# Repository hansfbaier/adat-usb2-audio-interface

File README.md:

# ADAT USB Audio Interface

FPGA based USB 2.0 High Speed audio interface featuring multiple optical ADAT inputs and outputs

## Status / current limitations
* Enumerates as class compliant audio device on Windows and Linux (Mac OS not tested). 2 and 32 channel modes.
* Audio input and output seems to work glitch free.
* Only 48kHz sample rate supported
* Integrated USB2 high speed logic analyzer works
* Runs without dropouts with FlexASIO with a buffer size of 32 samples (0.67ms latency)
* Has a hardware roundtrip latency (USB out -> ADAT out -> cable -> ADAT in -> USB in)
  of 2-3 USB2 microframes which is about 0.25ms to 0.375 ms
* Both headphone DACs on the board work now. In two channel mode, they are both wired to channels 0/1.
  In 36 channel mode DAC1 is wired to channels 0/1 and DAC2 to channels 2/3
* Both USB PHYs now are operational. USB1 has access to all 32 ADAT I/Os and has 4 extra channels to/from USB2.
  USB2 enumerates as a 4-channel sound card which sends/receives audio to/from USB1
* Both USB interfaces will also enumerate as USB MIDI devices and send each other MIDI
* The current board design has not been designed with the case in mind: In the current version of the case,
  only ADAT-cables with thin connectors will fit into the holes. Cables with fat connectors will hit the case
  wall before they can be fully inserted. This will be fixed in a future iteration of the PCB and case.
* The current case design lacks a guide channel for the LED light pipes. Therefore there is considerable bleed
  from lightpipes into each other, and they also can't be positioned exactly over the LEDs.
  Will be fixed in the next version of the case.
* Limitation: Currently audio input will not work properly when audio output is inactive.
  This should not be a problem for most uses (VoIP, Videoconference, DAW recording).
  If you have an important use case which needs this, please file an issue.

## Hardware
The current board design is a custom development board,
based on the QMTech core FPGA boards.
Once the chip shortage is over, it is planned to move to
a complete custom design, including the FPGA.

## How to build
1. Download and install [Intel Quartus Lite](https://fpgasoftware.intel.com/?edition=lite)
2. put the bin/ directory of Quartus into your PATH variable:
```bash
export PATH=$PATH:/opt/intelFPGA_lite/21.1/quartus/bin/
```
Of course you need to adjust this to the install directory and version of your particular installation.

3. Set up python venv and install requirements:
```bash
$ cd gateware/
$ ./initialize-python-environment.sh
$ cd ..
```

4. Activate the venv and build
```bash
$ source ./gateware/venv/bin/activate
$ python3 gateware/adat_usb2_audio_interface.py --keep
```

This will create a directory named build/ and after a successful build will directly
try to load the generated bitstream into the FPGA, if an USB-Blaster is connected.
Or, you can flash the bitstream manually, by opening the Quartus GUI with:
```bash
quartus build/*.qpf
```
and then open the programmer application from there.
Alternatively you could directly start the programmer with:
```bash
quartus_pgmw
```

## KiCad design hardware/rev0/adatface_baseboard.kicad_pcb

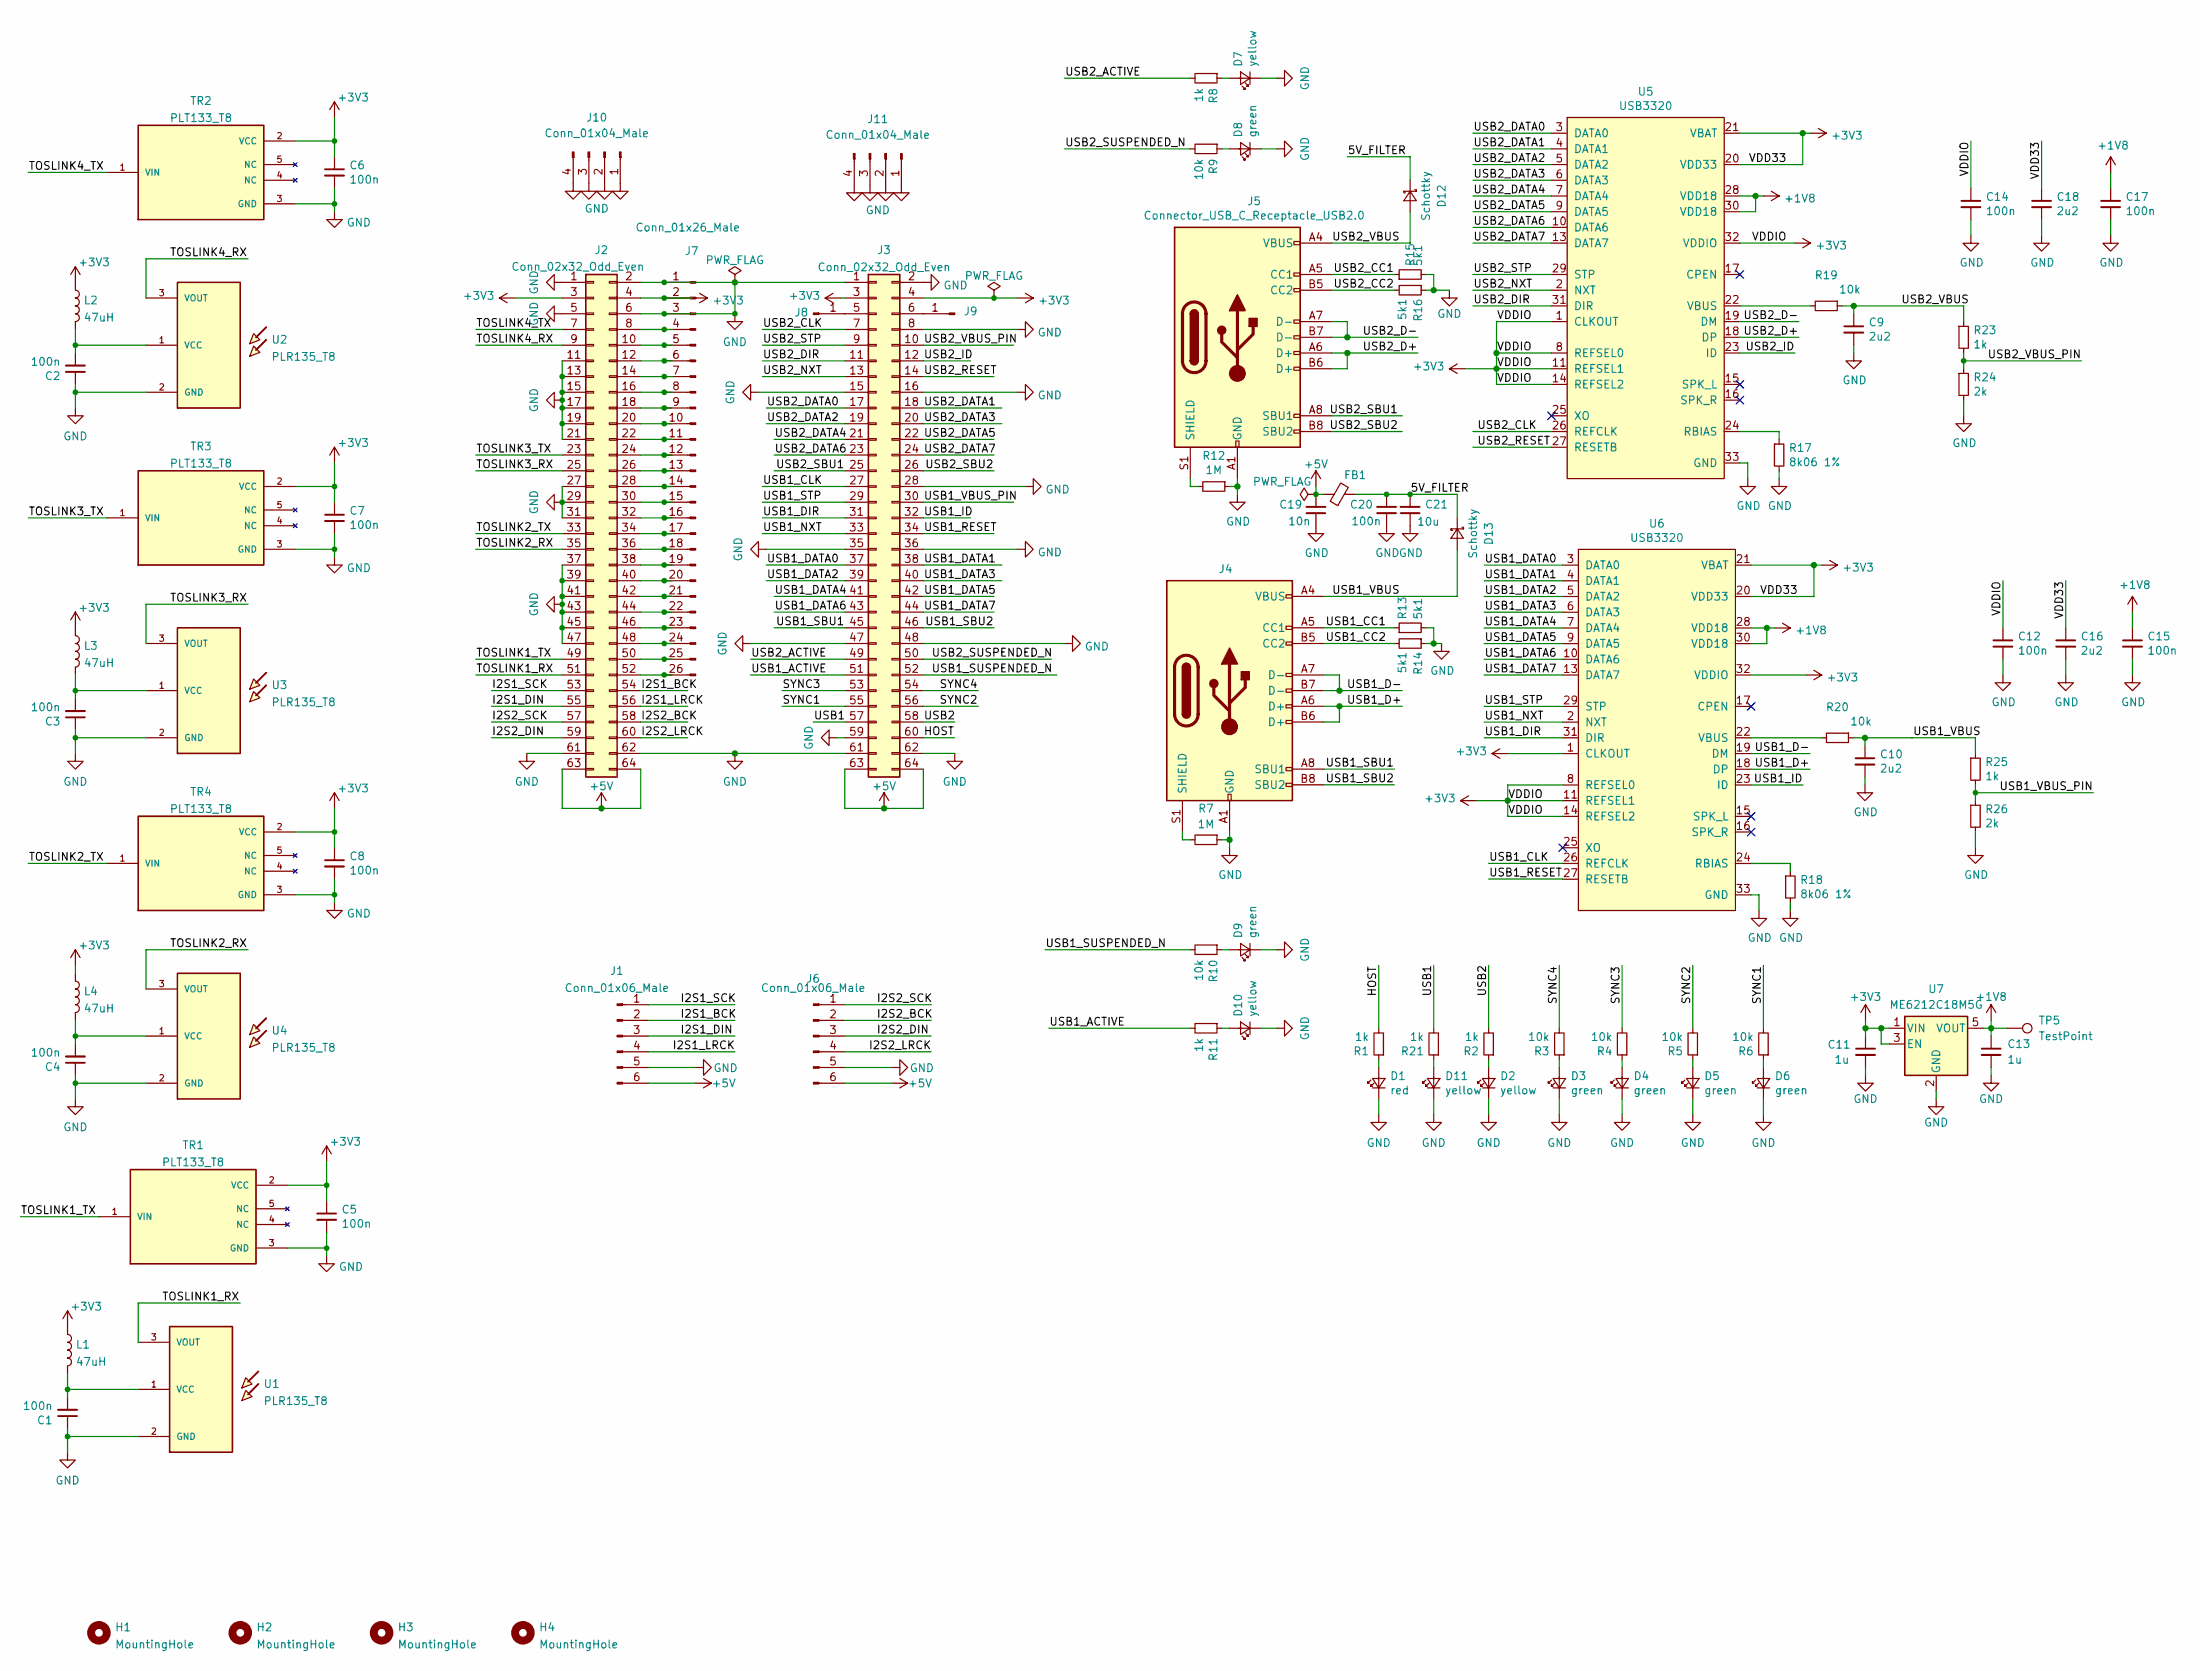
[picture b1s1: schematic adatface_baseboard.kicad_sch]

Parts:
C1, C2, C3, C4, C5, C6, C7, C8, C12, C14, C15, C17, C20: 100n; C_0603_1608Metric; LCSC C14663
C9, C10, C16, C18: 2u2; C_0603_1608Metric; LCSC C23630
C11, C13: 1u; C_0603_1608Metric; LCSC C15849
C19: 10n; C_0805_2012Metric; LCSC C1710
C21: 10u; C_0805_2012Metric; LCSC C15850
D1: red; LED_0603_1608Metric; LCSC C2286
D2, D7, D10, D11: yellow; LED_0603_1608Metric; LCSC C72038
D3, D4, D5, D6, D8, D9: green; LED_0603_1608Metric; LCSC C72043
D12, D13: Schottky; D_SMA; LCSC C22452
FB1: 1.5A; L_1206_3216Metric; LCSC C16902
H1, H2, H3, H4: MountingHole; MountingHole_3.2mm_M3_Pad_Via
J1, J6: Conn_01x06_Male; PinHeader_1x06_P2.54mm_Vertical
J2, J3: Conn_02x32_Odd_Even; PinHeader_2x32_P2.54mm_Vertical
J4, J5: Connector_USB_C_Receptacle_USB2.0; USB_C_Receptacle_XKB_U262-16XN-4BVC11; LCSC C165948
J7: Conn_01x26_Male; PinHeader_1x26_P2.54mm_Horizontal
J8, J9: Conn_01x01_Male; PinHeader_1x01_P2.54mm_Horizontal
J10, J11: Conn_01x04_Male; PinHeader_1x04_P2.54mm_Horizontal
L1, L2, L3, L4: 47uH; L_0805_2012Metric; LCSC C14304
R1, R2, R8, R11, R21, R23, R25: 1k; R_0603_1608Metric; LCSC C21190
R3, R4, R5, R6, R9, R10, R19, R20: 10k; R_0603_1608Metric; LCSC C25804
R7, R12: 1M; R_0603_1608Metric; LCSC C22935
R13, R14, R15, R16: 5k1; R_0603_1608Metric; LCSC C23186
R17, R18: 8k06 1%; R_0603_1608Metric; LCSC C23112
R24, R26: 2k; R_0603_1608Metric; LCSC C22975
TP5: TestPoint; TestPoint_Pad_D1.5mm
TR1, TR2, TR3, TR4: PLT133_T8; PARTREV 5
U1, U2, U3, U4: PLR135_T8; PLR135-T8_PLT133-T8
U5, U6: USB3320; QFN-32-1EP_5x5mm_P0.5mm_EP3.3x3.3mm; LCSC C132156
U7: ME6212C18M5G; SOT-23-5; LCSC C236669

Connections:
+1V8: C13.1, C15.1, C17.1, TP5.1, U5.28 (VDD18), U5.30 (VDD18), U6.28 (VDD18), U6.30 (VDD18), U7.5 (VOUT)
+3V3: C5.1, C6.1, C7.1, C8.1, C11.1, C12.1, C14.1, C16.1, C18.1, J2.3, J2.4, J3.3, J3.4, J7.2, L1.1, L2.1, L3.1, L4.1, TR1.2 (VCC), TR2.2 (VCC), TR3.2 (VCC), TR4.2 (VCC), U5.1 (CLKOUT), U5.8 (REFSEL0), U5.11 (REFSEL1), U5.14 (REFSEL2), U5.20 (VDD33), U5.21 (VBAT), U5.32 (VDDIO), U6.1 (CLKOUT), U6.8 (REFSEL0), U6.11 (REFSEL1), U6.14 (REFSEL2), U6.20 (VDD33), U6.21 (VBAT), U6.32 (VDDIO), U7.1 (VIN), U7.3 (EN)
+5V: C19.2, FB1.1, J1.6, J2.63, J2.64, J3.63, J3.64, J6.6
/5V_FILTER: C20.2, C21.2, D12.1 (K), D13.1 (K), FB1.2
/HOST: J3.60, R1.2
/I2S1_BCK: J1.2, J2.54
/I2S1_DIN: J1.3, J2.55
/I2S1_LRCK: J1.4, J2.56
/I2S1_SCK: J1.1, J2.53
/I2S2_BCK: J2.58, J6.2
/I2S2_DIN: J2.59, J6.3
/I2S2_LRCK: J2.60, J6.4
/I2S2_SCK: J2.57, J6.1
/SYNC1: J3.55, R6.2
/SYNC2: J3.56, R5.2
/SYNC3: J3.53, R4.2
/SYNC4: J3.54, R3.2
/TOSLINK1_RX: J2.51, U1.3 (VOUT)
/TOSLINK1_TX: J2.49, TR1.1 (VIN)
/TOSLINK2_RX: J2.35, U4.3 (VOUT)
/TOSLINK2_TX: J2.33, TR4.1 (VIN)
/TOSLINK3_RX: J2.25, U3.3 (VOUT)
/TOSLINK3_TX: J2.23, TR3.1 (VIN)
/TOSLINK4_RX: J2.9, U2.3 (VOUT)
/TOSLINK4_TX: J2.7, TR2.1 (VIN)
/USB1: J3.57, R21.2
/USB1_ACTIVE: J3.51, R11.2
/USB1_CC1: J4.A5 (CC1), R13.1
/USB1_CC2: J4.B5 (CC2), R14.2
/USB1_CLK: J3.27, U6.26 (REFCLK)
/USB1_D+: J4.A6 (D+), J4.B6 (D+), U6.18 (DP)
/USB1_D-: J4.A7 (D-), J4.B7 (D-), U6.19 (DM)
/USB1_DATA0: J3.37, U6.3 (DATA0)
/USB1_DATA1: J3.38, U6.4 (DATA1)
/USB1_DATA2: J3.39, U6.5 (DATA2)
/USB1_DATA3: J3.40, U6.6 (DATA3)
/USB1_DATA4: J3.41, U6.7 (DATA4)
/USB1_DATA5: J3.42, U6.9 (DATA5)
/USB1_DATA6: J3.43, U6.10 (DATA6)
/USB1_DATA7: J3.44, U6.13 (DATA7)
/USB1_DIR: J3.31, U6.31 (DIR)
/USB1_ID: J3.32, U6.23 (ID)
/USB1_NXT: J3.33, U6.2 (NXT)
/USB1_RESET: J3.34, U6.27 (RESETB)
/USB1_SBU1: J3.45, J4.A8 (SBU1)
/USB1_SBU2: J3.46, J4.B8 (SBU2)
/USB1_STP: J3.29, U6.29 (STP)
/USB1_SUSPENDED_N: J3.52, R10.2
/USB1_VBUS: C10.1, D13.2 (A), J4.A4 (VBUS), J4.A9 (VBUS), J4.B4 (VBUS), J4.B9 (VBUS), R20.1, R25.1
/USB1_VBUS_PIN: J3.30, R25.2, R26.1
/USB2: J3.58, R2.2
/USB2_ACTIVE: J3.49, R8.2
/USB2_CC1: J5.A5 (CC1), R15.1
/USB2_CC2: J5.B5 (CC2), R16.2
/USB2_CLK: J3.7, U5.26 (REFCLK)
/USB2_D+: J5.A6 (D+), J5.B6 (D+), U5.18 (DP)
/USB2_D-: J5.A7 (D-), J5.B7 (D-), U5.19 (DM)
/USB2_DATA0: J3.17, U5.3 (DATA0)
/USB2_DATA1: J3.18, U5.4 (DATA1)
/USB2_DATA2: J3.19, U5.5 (DATA2)
/USB2_DATA3: J3.20, U5.6 (DATA3)
/USB2_DATA4: J3.21, U5.7 (DATA4)
/USB2_DATA5: J3.22, U5.9 (DATA5)
/USB2_DATA6: J3.23, U5.10 (DATA6)
/USB2_DATA7: J3.24, U5.13 (DATA7)
/USB2_DIR: J3.11, U5.31 (DIR)
/USB2_ID: J3.12, U5.23 (ID)
/USB2_NXT: J3.13, U5.2 (NXT)
/USB2_RESET: J3.14, U5.27 (RESETB)
/USB2_SBU1: J3.25, J5.A8 (SBU1)
/USB2_SBU2: J3.26, J5.B8 (SBU2)
/USB2_STP: J3.9, U5.29 (STP)
/USB2_SUSPENDED_N: J3.50, R9.2
/USB2_VBUS: C9.1, D12.2 (A), J5.A4 (VBUS), J5.A9 (VBUS), J5.B4 (VBUS), J5.B9 (VBUS), R19.1, R23.1
/USB2_VBUS_PIN: J3.10, R23.2, R24.1
GND: C1.1, C2.1, C3.1, C4.1, C5.2, C6.2, C7.2, C8.2, C9.2, C10.2, C11.2, C12.2, C13.2, C14.2, C15.2, C16.2, C17.2, C18.2, C19.1, C20.1, C21.1, D1.1 (K), D2.1 (K), D3.1 (K), D4.1 (K), D5.1 (K), D6.1 (K), D7.1 (K), D8.1 (K), D9.1 (K), D10.1 (K), D11.1 (K), J1.5, J2.1, J2.2, J2.5, J2.6, J2.11, J2.13, J2.15, J2.17, J2.19, J2.21, J2.27, J2.29, J2.31, J2.37, J2.39, J2.41, J2.43, J2.45, J2.47, J2.61, J2.62, J3.1, J3.2, J3.8, J3.15, J3.16, J3.28, J3.35, J3.36, J3.47, J3.48, J3.59, J3.61, J3.62, J4.A1 (GND), J4.A12 (GND), J4.B1 (GND), J4.B12 (GND), J5.A1 (GND), J5.A12 (GND), J5.B1 (GND), J5.B12 (GND), J6.5, J7.1, J7.3, J10.1, J10.2, J10.3, J10.4, J11.1, J11.2, J11.3, J11.4, R7.1, R12.1, R13.2, R14.1, R15.2, R16.1, R17.2, R18.2, R24.2, R26.2, TR1.3 (GND), TR2.3 (GND), TR3.3 (GND), TR4.3 (GND), U1.2 (GND), U2.2 (GND), U3.2 (GND), U4.2 (GND), U5.33 (GND), U6.33 (GND), U7.2 (GND)
unnamed: C1.2, L1.2, U1.1 (VCC)
unnamed: C2.2, L2.2, U2.1 (VCC)
unnamed: C3.2, L3.2, U3.1 (VCC)
unnamed: C4.2, L4.2, U4.1 (VCC)
unnamed: D1.2 (A), R1.1
unnamed: D2.2 (A), R2.1
unnamed: D3.2 (A), R3.1
unnamed: D4.2 (A), R4.1
unnamed: D5.2 (A), R5.1
unnamed: D6.2 (A), R6.1
unnamed: D7.2 (A), R8.1
unnamed: D8.2 (A), R9.1
unnamed: D9.2 (A), R10.1
unnamed: D10.2 (A), R11.1
unnamed: D11.2 (A), R21.1
unnamed: J2.8, J7.4
unnamed: J2.10, J7.5
unnamed: J2.12, J7.6
unnamed: J2.14, J7.7
unnamed: J2.16, J7.8
unnamed: J2.18, J7.9
unnamed: J2.20, J7.10
unnamed: J2.22, J7.11
unnamed: J2.24, J7.12
unnamed: J2.26, J7.13
unnamed: J2.28, J7.14
unnamed: J2.30, J7.15
unnamed: J2.32, J7.16
unnamed: J2.34, J7.17
unnamed: J2.36, J7.18
unnamed: J2.38, J7.19
unnamed: J2.40, J7.20
unnamed: J2.42, J7.21
unnamed: J2.44, J7.22
unnamed: J2.46, J7.23
unnamed: J2.48, J7.24
unnamed: J2.50, J7.25
unnamed: J2.52, J7.26
unnamed: J3.5, J8.1
unnamed: J3.6, J9.1
unnamed: J4.S1 (SHIELD), R7.2
unnamed: J5.S1 (SHIELD), R12.2
unnamed: R17.1, U5.24 (RBIAS)
unnamed: R18.1, U6.24 (RBIAS)
unnamed: R19.2, U5.22 (VBUS)
unnamed: R20.2, U6.22 (VBUS)

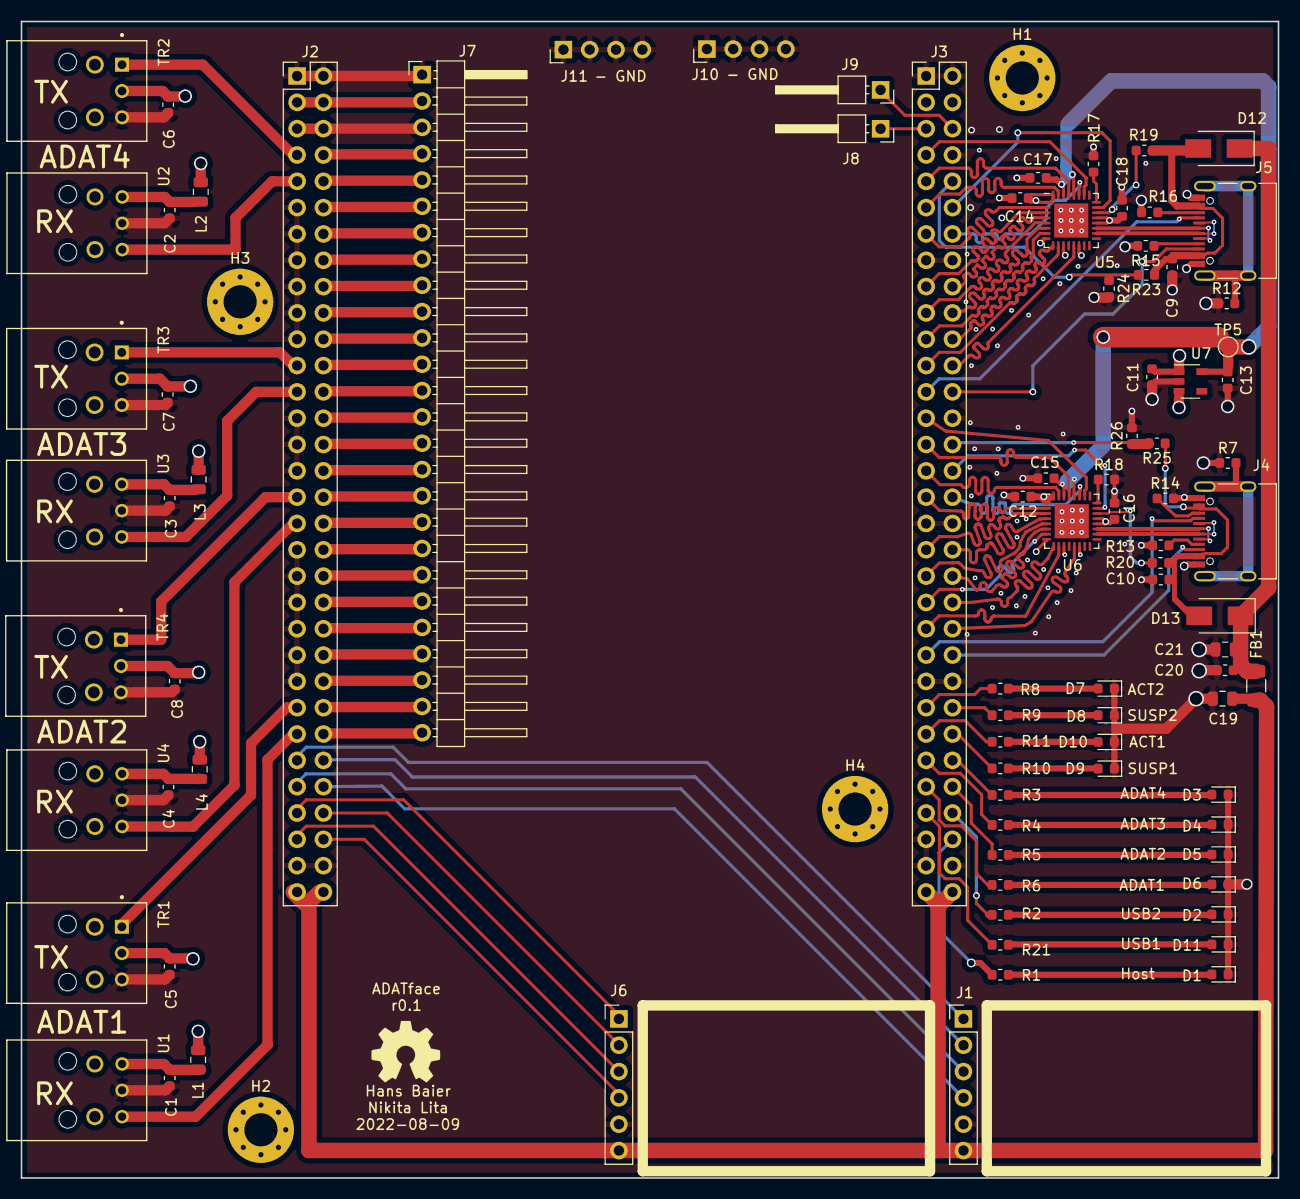
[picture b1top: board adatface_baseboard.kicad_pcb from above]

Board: 4 copper layers, 121.3 x 111.6 mm, 92 parts (0 on the bottom side), 122 nets.

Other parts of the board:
N1: OHWLOGO; OSHW-Symbol_6.7x6mm_SilkScreen

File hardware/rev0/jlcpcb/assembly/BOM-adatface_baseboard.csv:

Comment,Designator,Footprint,LCSC
10k,"R10,R3,R4,R5,R6,R9",R_0603_1608Metric, C25804
USB3320,"U5,U6",QFN-32-1EP_5x5mm_P0.5mm_EP3.3x3.3mm,C132156
PLR135_T8,"U1,U2,U3,U4",PLR135-T8_PLT133-T8,C133351
47uH,"L1,L2,L3,L4",L_0805_2012Metric,C14304
100n,"C1,C12,C14,C15,C17,C2,C20,C3,C4,C5,C6,C7,C8",C_0603_1608Metric,C14663
1u,"C11,C13",C_0603_1608Metric,C15849
10u,C21,C_0805_2012Metric,C15850
Connector_USB_C_Receptacle_USB2.0,"J4,J5",USB_C_Receptacle_XKB_U262-16XN-4BVC11,C165948
1.5A,FB1,L_1206_3216Metric,C16902
10n,C19,C_0805_2012Metric,C1710
1k,"R1,R11,R2,R21,R23,R25,R8",R_0603_1608Metric,C21190
Schottky,"D12,D13",D_SMA,C22452
red,D1,LED_0603_1608Metric,C2286
1M,"R12,R7",R_0603_1608Metric,C22935
2k,"R24,R26",R_0603_1608Metric,C22975
8k06 1%,"R17,R18",R_0603_1608Metric,C23112
5k1,"R13,R14,R15,R16",R_0603_1608Metric,C23186
2u2,"C10,C16,C18,C9",C_0603_1608Metric,C23630
ME6212C18M5G,U7,SOT-23-5,C236669
10k,"R19,R20",R_0603_1608Metric,C25804
PLT133_T8,"TR1,TR2,TR3,TR4",PLT133_T8,C2940206
yellow,"D10,D11,D2,D7",LED_0603_1608Metric,C72038
green,"D3,D4,D5,D6,D8,D9",LED_0603_1608Metric,C72043
MountingHole,H3,MountingHole_3.2mm_M3_Pad_Via,
MountingHole,H4,MountingHole_3.2mm_M3_Pad_Via,
Conn_02x32_Odd_Even,J3,PinHeader_2x32_P2.54mm_Vertical,
Conn_01x26_Male,J7,PinHeader_1x26_P2.54mm_Horizontal,
Conn_01x06_Male,J6,PinHeader_1x06_P2.54mm_Vertical,
TestPoint,TP5,TestPoint_Pad_D1.5mm,
Conn_01x01_Male,J9,PinHeader_1x01_P2.54mm_Horizontal,
MountingHole,H2,MountingHole_3.2mm_M3_Pad_Via,
Conn_01x06_Male,J1,PinHeader_1x06_P2.54mm_Vertical,
Conn_01x01_Male,J8,PinHeader_1x01_P2.54mm_Horizontal,
MountingHole,H1,MountingHole_3.2mm_M3_Pad_Via,
Conn_02x32_Odd_Even,J2,PinHeader_2x32_P2.54mm_Vertical,
Conn_01x04_Male,J11,PinHeader_1x04_P2.54mm_Horizontal,
Conn_01x04_Male,J10,PinHeader_1x04_P2.54mm_Horizontal,

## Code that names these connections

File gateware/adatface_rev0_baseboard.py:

from amaranth.build import *
from amaranth_boards.resources import *

class ADATFaceRev0Baseboard:
    @staticmethod
    def resources(attrs, colorlight=False):
        return [
            # LEDS
            Resource("leds", 0,
                Subsignal("host",       Pins ("J_3:60", dir="o")),
                Subsignal("usb1",       Pins ("J_3:57", dir="o")),
                Subsignal("usb2",       Pins ("J_3:58", dir="o")),
                Subsignal("sync1",      Pins ("J_3:55", dir="o")),
                Subsignal("sync2",      Pins ("J_3:56", dir="o")),
                Subsignal("sync3",      Pins ("J_3:53", dir="o")),
                Subsignal("sync4",      Pins ("J_3:54", dir="o")),
                Subsignal("active1",    Pins ("J_3:51", dir="o")),
                Subsignal("active2",    Pins ("J_3:49", dir="o")),
                Subsignal("suspended1", Pins ("J_3:52", dir="o")),
                Subsignal("suspended2", Pins ("J_3:50", dir="o")),
                attrs),


            # USB
            ULPIResource("ulpi", 1,
                data="J_3:37 J_3:38 J_3:39 J_3:40 J_3:41 J_3:42 J_3:43 J_3:44",
                clk="J_3:27", clk_dir="o", # this needs to be a clock pin of the FPGA or the core won't work
                dir="J_3:31", nxt="J_3:33", stp="J_3:29", rst="J_3:34", rst_invert=True, # USB3320 reset is active low
                attrs=attrs),

            Resource("usb_aux", 1,
                Subsignal("vbus", Pins("J_3:30", dir="i")),
                Subsignal("id",   Pins("J_3:32", dir="o")),
                Subsignal("sbu1", Pins("J_3:45", dir="i")),
                Subsignal("sbu2", Pins("J_3:46", dir="i")),
                attrs),

            ULPIResource("ulpi", 2,
                data="J_3:17 J_3:18 J_3:19 J_3:20 J_3:21 J_3:22 J_3:23 J_3:24",
                clk="J_3:7", clk_dir="o", # this needs to be a clock pin of the FPGA or the core won't work
                dir="J_3:11", nxt="J_3:13", stp="J_3:9", rst="J_3:14", rst_invert=True, # USB3320 reset is active low
                attrs=attrs),

            Resource("usb_aux", 2,
                Subsignal("vbus", Pins("J_3:10", dir="i")),
                Subsignal("id",   Pins("J_3:12", dir="o")),
                Subsignal("sbu1", Pins("J_3:25", dir="i")),
                Subsignal("sbu2", Pins("J_3:26", dir="i")),
                attrs),

            Resource("i2s", 1,
                Subsignal("sclk",   Pins("J_2:53", dir="o")),
                Subsignal("bclk",   Pins("J_2:54", dir="o")),
                Subsignal("data",   Pins("J_2:55", dir="o")),
                Subsignal("lrclk",  Pins("J_2:56", dir="o")),
                attrs),

            Resource("i2s", 2,
                Subsignal("sclk",   Pins("J_2:57", dir="o")),
                Subsignal("bclk",   Pins("J_2:58", dir="o")),
                Subsignal("data",   Pins("J_2:50", dir="o") if colorlight else Pins("J_2:59", dir="o")),
                Subsignal("lrclk",  Pins("J_2:52", dir="o") if colorlight else Pins("J_2:60", dir="o")),
                attrs),


            # TOSLINK
            Resource("toslink", 1,
                Subsignal("tx", Pins("J_2:49", dir="o")),
                Subsignal("rx", Pins("J_2:51", dir="i")),
                attrs),

            Resource("toslink", 2,
                Subsignal("tx", Pins("J_2:33", dir="o")),
                Subsignal("rx", Pins("J_2:35", dir="i")),
                attrs),

            Resource("toslink", 3,
                Subsignal("tx", Pins("J_2:23", dir="o")),
                Subsignal("rx", Pins("J_2:25", dir="i")),
                attrs),

            Resource("toslink", 4,
                Subsignal("tx", Pins("J_2:18", dir="o") if colorlight else Pins("J_2:7", dir="o")),
                Subsignal("rx", Pins("J_2:9", dir="i")),
                attrs),


            # Debug
            SPIResource(0, clk="J_2:12", copi="J_2:8", cipo=None, cs_n="J_2:10", attrs=attrs),
            #UARTResource(0, tx="J_2:14", rx="J_2:16", attrs=attrs),

            Resource("debug", 0, Pins("J_2:44", dir="o")),
            Resource("debug", 1, Pins("J_2:46", dir="o")),
            Resource("debug", 2, Pins("J_2:48", dir="o")),
            Resource("debug", 3, Pins("J_2:42", dir="o")),
        ]

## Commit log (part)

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2021-07-17 change LICENSE
2021-07-17 rename main python file to be consistent with project name
2021-07-17 use pid.codes test PID
2021-07-20 New USB IDs
2021-07-20 fix wrong control interface number
2021-07-20 fix wrong endpoint attributes
2021-07-20 fix sample rate resolution
2021-07-27 tidy imports
2021-07-27 fix endpoint attributes
2021-07-27 comment out quite alternate settings
2021-07-27 square-ish input signal
2021-07-28 reinstate quiet alternate settings
2021-07-28 send feedback data
2021-07-28 descriptor: make clock id unique and shift all other ids by one
2021-07-28 make test input signal non-dc
2021-07-30 adapt to new isochronous endpoint classes
2021-07-31 add debug GPIOs to platform
2021-07-31 use newly created stream IN endpoint for audio input
2021-08-02 disable debug
2021-08-02 get rid of unnecessary latency due to buffering in stream out enpoint
2021-08-02 update gitignore
2021-08-04 usb_stream_to_channels: implement first and last on output, rename usb to sync domain
2021-08-05 parameterize number of channels and wire usb out stream to ADAT tramsmitter
2021-08-06 usb_stream_to_channels: fix wrong byte order
2021-08-08 use pickled ILA
2021-08-08 revert wrong fix d1ffdaf919d9d10e25b3b3361a95cb9046e2e8eb
2021-08-09 usb_stream_to_channels: make it work with 8 channels
2021-08-09 activate all 8 channels and prepare ILA for feedback control
2021-08-12 implement rate feedback and make IN frame bytes follow out frame bytes
2021-08-12 fix ILA depth, must be int
2021-08-12 factor out request handlers into own file
2021-08-12 fix ILA pretrigger size and update README
2021-08-13 fix bug: insufficient channel number bits, add settings changed signal
2021-08-25 reimplement usb_stream_to_channels as state machine
2021-08-25 usb_stream_to_channels: remove debug print
2021-08-26 clean for pull request
2021-08-26 make number of channels and bitwidth configurable by the platform
2021-08-31 got audio channel to usb stream converter ready
2021-08-31 fix clock domains
2021-08-31 usb_stream_to_channels: make it work for variable number of channels
2021-09-01 fix var name: channel_no -> channel_nr, fix usb to audio stream converter
2021-09-04 channels_to_usb_stream: make it robust against underflows/overflows
2021-09-11 Add Support for QMTech EP4CE15 with ULPI PMod on daughterboard
2021-09-11 QMTech XC7A35T board finally works with Tobias Müller's Pmod and the QMTech daughterboard.
2021-10-06 Add baseboard EDA files and adjust platform files accordingly
2021-10-06 rename top level submodules according to board
2021-10-07 unify EP4CE* platforms into one file
2021-10-07 rename adat pads
2021-11-06 add debug display and invert suspended LEDs
2021-11-06 factor out USB descriptor generation into its own class
2021-11-06 correct off by one error in feedback calculation
2021-11-06 make debug display work
2021-11-09 fix bug: whole design optimized away
2021-11-09 fix silent audio (channel payload width was 8)
2021-11-09 add timing annotations (constrain CDCs and derive clock uncertainties)
2021-11-10 fix audio input frame size calculation
2021-11-10 tidy imports in top level file
2021-11-10 channels_to_usb: fix stream names
2021-11-13 README
2021-11-13 README: add images
2021-11-21 channels_to_usb: fix: don't discard valid samples on underrun
2021-11-25 .gtkwaverc: Add shortcuts
2021-11-25 Get Audio feedback right
2021-11-25 channels_to_usb_stream: make it more robust against garbled input
2021-11-25 pcb: update to KiCAD 6
2021-11-26 channels_to_usb_stream: fix bug: whole USB frame misaligned
2021-11-30 Fix bugs in rev0
2021-12-03 hardware: fix header width and 3d model paths
2021-12-03 add WIP case design
2021-12-03 case: fix height and chamfer case at the end
2021-12-05 case: fine tune parameters
2021-12-05 case: convert top lid case into bottom lid case
2021-12-05 case: Add BottomRightSupport
2021-12-05 case: add lightpipe chamfer
2021-12-05 case: add lightpipe dummys
2021-12-06 case: add LED legend
2021-12-06 case: add debug LED holes and lightpipes
2021-12-06 case: case body is done
2021-12-06 case: case body chamfers, add screws
2021-12-08 adapt case height to correct value and parameterize height of letters
2021-12-08 add missing USB descriptors file, and yay, we got our own USB device ID
2021-12-09 ila.py: adapt to new USB device ID
2021-12-09 channels_to_usb: make sure that the input of the module does not drop samples
2021-12-11 sightly refactor feedback
2021-12-11 ILA: add more debug signals, set it up to debug the ADAT signals directly
2021-12-13 top level: add comments for the different sections of the design
2021-12-13 rename usb1_to_adat_fifo -> usb1_to_output_fifo
2021-12-13 comments
2021-12-13 CRG: rename soundpll to audiopll and make the ADAT transmit domain a multiple of the sampling frequency
2021-12-13 create BundleDemultiplexer
2021-12-14 revert ADAT receiver frequency parameter to 100MHz as it - strangely enough - does not work with the correct frequency
2021-12-14 Revert "revert ADAT receiver frequency parameter to 100MHz as it - strangely enough - does not work with the correct frequency" Was a mistake in my test harness. It actually works.
    This reverts commit 0f6e38a8b43d566664339f1168e55fb45d428b18.
2021-12-14 implement bundle multiplexer
2021-12-15 bundle_multiplexer test: test data not ready
2021-12-15 refactor: extract methods for calculating audio input frame size and rate feedback
2021-12-15 activate and wire up all 4 ADAT transmitters/receivers
2021-12-16 fix wrong channel number setting
2021-12-16 fix missing ready wire
2021-12-16 better timing for debug display
2021-12-16 rename usb1_to_... => usb_to_...
2021-12-17 bundle_multiplexer: fix missing last wire, add debug signals, add ILA signal set
2021-12-17 bundle_multiplexer: nicer name for input bundles
2021-12-21 channels_to_usb_stream: fix channel number bitwidth
2021-12-22 nmigen => amaranth rename
2021-12-22 extract variables for better readability
2021-12-22 ILA configuration for debugging multiplexers/demultiplexers
2021-12-22 adjust feedback loop do it does not overflow with 32 channels
2021-12-22 make sync domain run at a multiple of ADAT speed. This helps CDC timing
2021-12-22 sync debug: more samples and correct samplerate
2021-12-23 add ILA debugging signals
2021-12-23 channels_to_usb_stream: add fifo_full debug signal and extract variable fifo_depth; increase fifo_depth
2021-12-23 bundle_demultiplexer: fix wrong last_channel signal
2021-12-23 show wave highlight in gtkwave
2021-12-23 trim excessive FIFO sizes (they overflow anyway), cosmetic code changes, add debug signals
2021-12-23 Now it mostly seems to work, with the ILA enabled and at that place. But we still are losing samples at input.
2021-12-23 bundle_multiplexer: have the receiver FIFOs three audio samples
2021-12-23 whitespace
2021-12-23 factor out ILA setup into method
2021-12-24 ILA: add channel receive/transmit counters
2021-12-25 bundle_multiplexer: refactor logic
2021-12-25 add testbench gtkw file for bundle_multiplexer
2021-12-25 add some gaps into the bundle_multiplexer test bench
2021-12-25 ILA: monitor transmit and receive frame rates
2021-12-25 bundle_multiplexer bench: add another gap
2021-12-27 insert missing cdc for number of channels
2021-12-28 amaranth_library => amlib rename
2021-12-29 ILA: configure to monitor frame rates throughout the signal path
2021-12-30 ILA/Debug LED matrix: add receiver rate debug and add graphical FIFO level bars
2021-12-30 debug matrix: better signal names
2021-12-30 make input CDC FIFO bigger, it was too small before
2021-12-30 add rx fifo levels output to multiplexer for debug display
2021-12-30 bundle_multiplexer test: fix gtkw file and add test
2021-12-30 factor out debug LED array into its own method and deactivate by default
2021-12-30 reduce unnecessary resource usage by several thousand LUTs/FFs
2021-12-31 give the multiplexer FIFOs enough space
2021-12-31 bundle_multiplexer bench: add new test with all channels sending at once
2021-12-31 extract stereo signal from USB out stream and wire it into DAC1
2022-01-01 fix DAC playback (fist and last flags missing, channel is irrelevant)
2022-01-01 wire up second DAC
2022-01-01 using a buffered FIFO uses block RAM and does not generate FFs
2022-01-01 wire the second DAC to main stereo pair if two channel mode is active
2022-01-01 fix swapped left/right channels in DACs
2022-01-03 separate code for main signal paths
2022-01-03 wire up channel stream combiner
2022-01-03 fix syntax errors of last commits
2022-01-03 a maximum of 6 channels is possible on the secondary USB interface
2022-01-03 properly detect if USB2 audio out is active
2022-01-03 Fix channel stream combiner
2022-01-04 fix amlib imports
2022-01-04 fix channel combiner
2022-01-04 remove bad import
2022-01-04 fix ILA variables and add debug signal to combiner
2022-01-04 fix USB2 channels active signal
2022-01-05 fix usb2 endpoint parameters
2022-01-05 fix channel combiner and add basic test case
2022-01-05 fix max packet sizes
2022-01-05 fix wrong domain of USB2->USB1 FIFO and debug display
2022-01-06 add channel stream splitter
2022-01-06 wire up USB2 audio input to USB1 audio output (upper channels)
2022-01-07 debug channel splitter
2022-01-07 debug USB2 audio IN
2022-01-07 remove redundant assignment
2022-01-07 fix bug: usb2_ep2_in did not have the needed frame size set
2022-01-08 use new ADAT transmitter core and add logic analyzer for it
2022-01-09 refactor platform files and add Cyclone V platform
2022-01-10 fix Cyclone10 platform
2022-01-11 factor out depth of USB MIDI FIFOs and add debug display for their levels
2022-01-11 fix USB MIDI: MIDI FIFOs were in the wrong clock domain
2022-01-12 MIDI: MaxPacketSize FIFO depth is more than enough
2022-01-15 first try at multiple audio clock support (currently hangs the fitter)
2022-01-16 avoid clock domain muxing in clock divided domains. Succeeds to build but takes 18min and not tested yet
2022-01-16 car: reorder clock domains
2022-01-17 add photo
2022-01-17 carry over some improvements from multiclock branch
2022-01-17 add block diagram source file
2022-01-17 README: add case image
2022-01-17 README: case image, again
2022-01-18 update BlockDiagram
2022-01-20 fix wrong audio in frame size calculation.
2022-01-20 channels_to_usb: simplify a bit
2022-01-21 It works! On the XC7A35T!
2022-01-21 make cyclone IV default again
2022-01-23 Using altera_pll instead of altpll for CycloneV now
2022-01-24 succesful synthesis with Cyclone V mode of altera_pll; but it does not connect to USB
2022-01-24 first try to build for kintex
2022-01-25 Cyclone V PLL is working now
2022-01-25 try to build with symbiflow
2022-01-27 add FUNDING.yml
2022-04-13 Added an optional convolver as dsp for the dac1 output. The convolver can be enabled with the USE_CONVOLUTION flag. Once the design has been synthesized with USE_CONVOLUTION enabled you can enable th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
2022-04-28 lattice PLL clock divider can't go beyond 128; use gateware clock divider for the DAC clock
2022-04-29 debug.py: fix exception when convolution is turned off
2022-06-11 add JT51synth submodule
2022-06-11 add colorlight platform to main file
2022-06-11 add minerva based soc with CPU/UART/Timer
2022-06-11 settings.json
2022-08-05 Fix missing symbol and footprint libraries for toslink
2022-08-05 change toslink footprints to T8 variation
    Footprint is the same except for the edition of NPTH for
    plastic mounting feet, so either T8 or T10 versions can
    be used.
2022-08-05 Update JLCPCB files
2022-08-06 Fix power trace board clearance issue, adjust board width for TOSLINK port clearance
2022-08-06 fix POS file
2022-08-06 adjust PHY1 diff pair trace widths
2022-08-06 move trace which was too close to the upper PHY diff pairs
2022-08-06 fix hole-hole spacing issues
2022-08-06 remove max PTH size rule;
    was producing bogus errors
2022-08-07 change default via sizes to match minimum annular width
2022-08-07 fix DRC errors
2022-08-09 baseboard rev0.1: Fix DRC rules with new KiCAD version, length matched USB PHY traces, more ground vias, fix trace spacing, ground headers
2022-08-09 Add back rules, change them so they don't interfere with zones
2022-08-09 fix reference designators on GND headers
2022-08-09 Add nikitalita to the credits on the board. Also adjust diff pair of the top PHY
2022-08-09 fix diff pair run on both top and bottom USB interfaces
2024-09-17 import SOC packages only if it is built with soc
